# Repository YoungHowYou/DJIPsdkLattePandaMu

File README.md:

# LattePandaMu_carrier_custom
LattePandaMu大疆无人机x-port专用开发板

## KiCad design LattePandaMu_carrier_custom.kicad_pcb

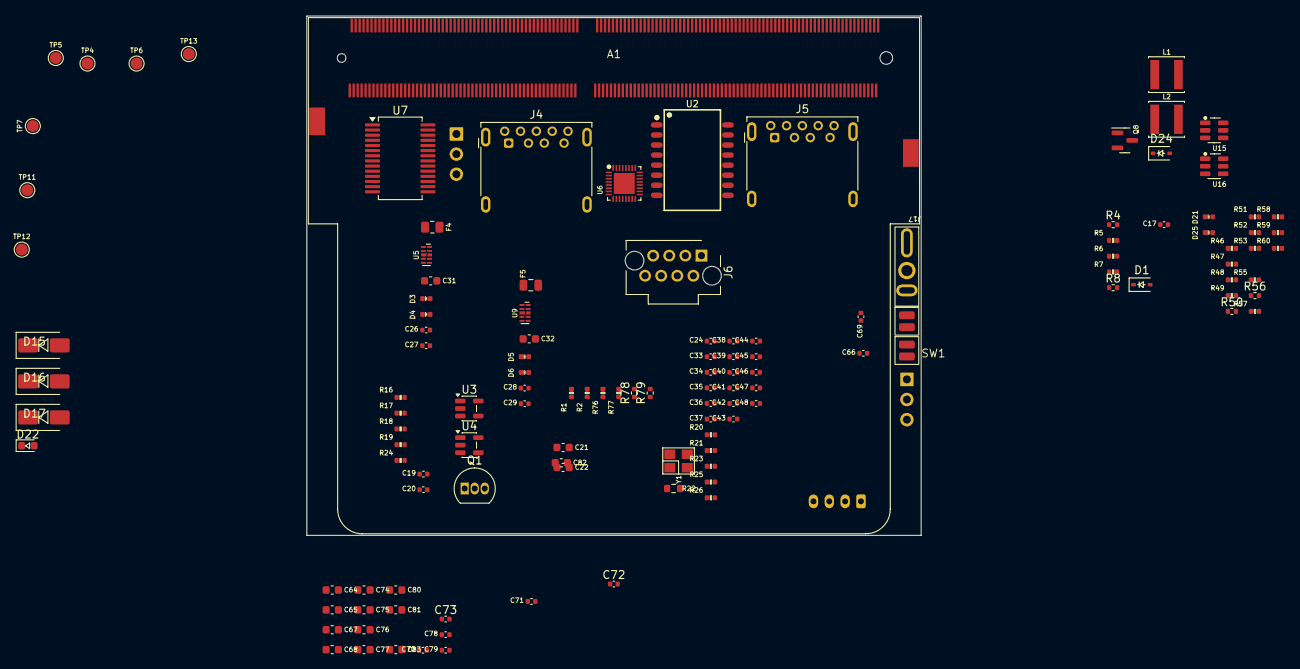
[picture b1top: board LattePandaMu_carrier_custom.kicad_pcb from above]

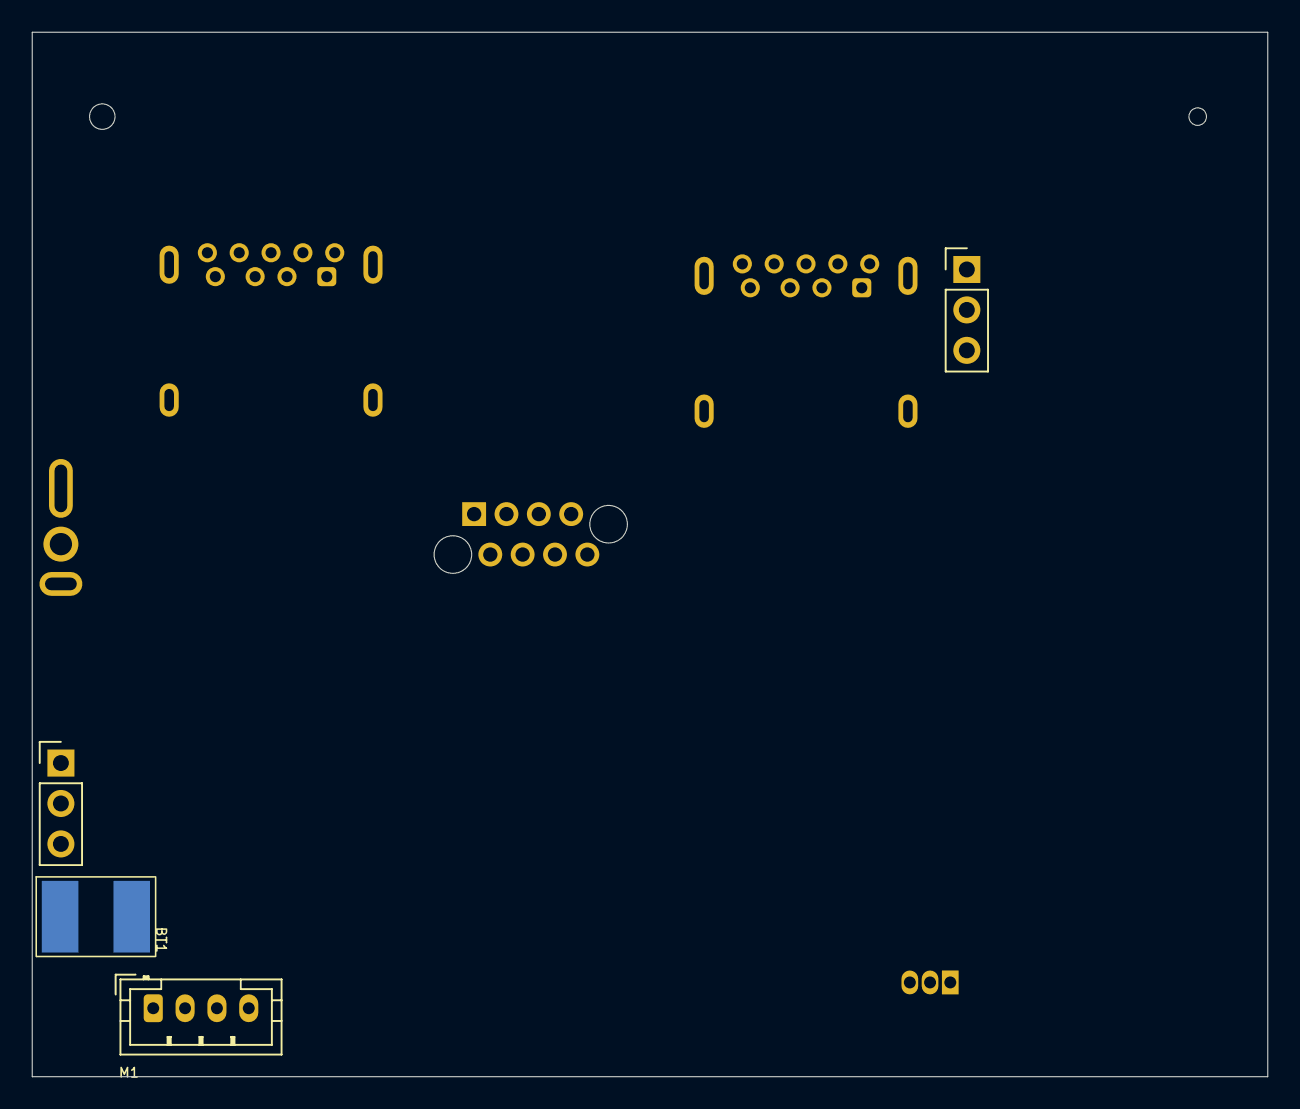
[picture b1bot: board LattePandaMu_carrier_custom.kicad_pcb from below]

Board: 4 copper layers, 77.6 x 65.6 mm, 130 parts (4 on the bottom side), 91 nets, no tracks yet.

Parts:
A1: LattePanda_Mu; LattePanda_Module_H8.0mm_Horizontal
BT1: Battery_Cell; Battery_Holder_CR1220_S8411-45R
C17, C26, C27, C28, C29, C33, C34, C35, C36, C37, C38, C39, C40, C41, C42, C43, C45, C48, C70, C71, C78, C79: 100nF/50V; C_0402_1005Metric
C19, C20, C66, C69: 1uF/16V; C_0402_1005Metric
C21, C22: 100nF; C_0603_1608Metric
C24: 1000pF/2kV; C_0402_1005Metric
C31, C32, C64, C65, C67, C68, C74, C75, C76, C77, C80, C81, C82, C83: 22uF/10V; C_0603_1608Metric
C44: 10uF/10V; C_0402_1005Metric
C46, C47, C72, C73: 12pF/50V; C_0402_1005Metric
D1: 1N5819WS; D_SOD-323
D3, D4, D5, D6, D21, D25: ESD5V0B03; D_0402_1005Metric
D15, D16, D17: SS54; D_SMA
D22: LED_G; LED_0603_1608Metric
D24: 3V3 Izt=5mA; D_SOD-323
F4: 6V/2A; R_0805_2012Metric
F5: 6V/2A; Fuse_0805_2012Metric
J1: Conn_01x03_Pin; PinHeader_1x03_P2.54mm_Vertical
J3: Conn_01x03; PinHeader_1x03_P2.54mm_Vertical
J4, J5: USB3_A; USB3_A_Molex_48393-001
J6: RJ45; RJ45_Plug_Metz_AJP92A8813
J17: Barrel_Jack_Switch; DC_Jack_DC007B_30V_10A
L1, L2: 2.2uH/4.3A; L_Sunlord_SWPA4020S
M1: Fan_4pin; JST_PH_B4B-PH-K_1x04_P2.00mm_Vertical
Q1: 2N3906; TO-92_Inline
Q8: 2N7002; SOT-23
R1, R47: 1K/1%; R_0402_1005Metric
R2, R16, R17, R18, R20, R21, R24, R49, R50, R56, R58, R78, R79: 10K/1%; R_0402_1005Metric
R4, R5, R60: 4.7K/1%; R_0402_1005Metric
R6, R8, R59: 21.5K/1%; R_0402_1005Metric
R7, R46, R48, R55: 100R/1%; R_0402_1005Metric
R19: 20K/1%; R_0402_1005Metric
R22: 2.49K/1%; R_0603_1608Metric
R23: 1M/1%; R_0402_1005Metric
R25, R26: 75/1%; R_0402_1005Metric
R51, R76, R77: 100K/1%; R_0402_1005Metric
R52, R53: 2.2K/1%; R_0402_1005Metric
R57: 75K/1%; R_0402_1005Metric
SW1, SW2: SW_Push; SW_Push_6x6x6
TP4, TP5, TP6, TP7, TP11, TP12, TP13: TestPoint; TestPoint_Pad_D1.5mm
U2: H1601-A; SOP-16_12.7x7.1-E1.27
U3: SN74LVC1G125DBV; SOT-23-5
U4: SN74LVC1G126DBV; SOT-23-5
U5, U9: ULC0524P; Diodes_UDFN-10_1.0x2.5mm_P0.5mm
U6: RTL8111H-CG-RH; QFN-32-1EP_4x4mm_P0.4mm_EP2.65x2.65mm
U7: FT232RL; SSOP-28_5.3x10.2mm_P0.65mm
U15, U16: SY8253ADC; TSOT-23-6
Y1: 25MHz; Crystal_SMD_3225-4Pin_3.2x2.5mm

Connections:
+1V0: C33.2, C34.2, C35.2, C36.2, C40.2, C44.2, U6.3 (AVDD10), U6.8 (AVDD10), U6.22 (DVDD10), U6.24 (REGOUT), U6.30 (AVDD10)
+3V3: C37.2, C41.2, C45.2, C73.1, C75.2, C77.2, C79.1, C81.2, C83.2, L2.2, R4.1, R20.1, R21.1, R50.2, R52.2, R56.2, R59.2, TP6.1, U6.11 (AVDD33), U6.23 (VDDREG), U6.32 (AVDD33)
+5V: C17.1, C19.2, C20.2, C31.2, C32.2, C72.1, C74.2, C76.2, C78.1, C80.2, C82.2, D1.1 (K), F4.1, F5.1, J3.2, L1.2, M1.2 (+), Q1.1 (E), R5.1, R16.1, R17.1, R24.2, R57.2, TP5.1, U3.5 (VCC), U4.5 (VCC), U7.4 (VCCIO)
+12V: D15.2 (A), D16.2 (A), D17.2 (A), J17.1, TP4.1
+BATT: A1.115 (VBAT), R1.1
/LattePanda Module/FAN_1_PWM: A1.2 (FAN1_PWM), R4.2, R7.1, TP12.1
/LattePanda Module/FAN_1_TAC: A1.4 (FAN1_TAC), R6.2, R8.1, TP11.1
/LattePanda Module/HSIO_0_RX+: A1.16 (HSIO0_RX+), J5.6 (SSRX+), U9.5, U9.6 (NC)
/LattePanda Module/HSIO_0_RX-: A1.18 (HSIO0_RX-), J5.5 (SSRX-), U9.4, U9.7 (NC)
/LattePanda Module/HSIO_0_TX+: A1.13 (HSIO0_TX+), C29.1
/LattePanda Module/HSIO_0_TX-: A1.15 (HSIO0_TX-), C28.1
/LattePanda Module/HSIO_1_RX+: A1.22 (HSIO1_RX+), J4.6 (SSRX+)
/LattePanda Module/HSIO_1_RX-: A1.24 (HSIO1_RX-), J4.5 (SSRX-), U5.4, U5.7 (NC)
/LattePanda Module/HSIO_1_TX+: A1.19 (HSIO1_TX+), C27.1
/LattePanda Module/HSIO_1_TX-: A1.21 (HSIO1_TX-), C26.1
/LattePanda Module/HSIO_6_RX+: A1.64 (HSIO6_RX+), C43.2
/LattePanda Module/HSIO_6_RX-: A1.66 (HSIO6_RX-), C39.2
/LattePanda Module/HSIO_6_TX+: A1.61 (HSIO6_TX+), C42.2
/LattePanda Module/HSIO_6_TX-: A1.63 (HSIO6_TX-), C38.2
/LattePanda Module/REFCLK4+: A1.94 (REFCLK4+), U6.15 (REFCLK_P)
/LattePanda Module/REFCLK4-: A1.96 (REFCLK4-), U6.16 (REFCLK_N)
/LattePanda Module/SOC_UART0_RX: A1.137 (UART0_RXD), R16.2, R18.2, U4.2
/LattePanda Module/SOC_UART0_TX: A1.139 (UART0_TXD), R17.2, U3.4
/LattePanda Module/USB_2_P1+: A1.69 (USB2_P1+), D5.2 (A2), J5.3 (D+)
/LattePanda Module/USB_2_P1-: A1.67 (USB2_P1-), D6.2 (A2), J5.2 (D-)
/LattePanda Module/USB_2_P2+: A1.75 (USB2_P2+), D4.2 (A2), J4.3 (D+)
/LattePanda Module/USB_2_P2-: A1.73 (USB2_P2-), D3.2 (A2), J4.2 (D-)
/LattePanda Module/USB_2_P5+: A1.111 (USB2_P5+), U7.15 (USBD+)
/LattePanda Module/USB_2_P5-: A1.109 (USB2_P5-), U7.16 (USBD-)
/LattePanda Module/~PLT_RST: A1.105 (~PLTRST), U6.19 (PERSTB)
/LattePanda Module/~PWR_LED/~PSON: A1.5 (SLS_S0), R46.1, R47.1
/LattePanda Module/~PWR_SW: A1.1 (~PWRBTN), R48.2
/LattePanda Module/~RST_SW: A1.3 (~RSTBTN), R55.2
/usb转ttl3.3vUART/RX: J6.8, U7.5 (RXD)
/usb转ttl3.3vUART/TX: J6.7, U7.1 (TXD)
/千兆网/HSI+: C42.1, U6.13 (HSIP)
/千兆网/HSI-: C38.1, U6.14 (HSIN)
/千兆网/HSO+: C43.1, U6.17 (HSOP)
/千兆网/HSO-: C39.1, U6.18 (HSON)
/千兆网/MDIN0: J6.1, U2.11
/千兆网/MDIN1: J6.3, U2.16
/千兆网/MDIP0: J6.2, U2.9
/千兆网/MDIP1: J6.6, U2.14
/电源/PWR_EN: R46.2, R51.2, U15.4 (EN), U16.4 (EN)
GND: A1.11 (GND), A1.14 (GND), A1.17 (GND), A1.20 (GND), A1.23 (GND), A1.26 (GND), A1.29 (GND), A1.32 (GND), A1.35 (GND), A1.38 (GND), A1.41 (GND), A1.44 (GND), A1.47 (GND), A1.50 (GND), A1.53 (GND), A1.56 (GND), A1.59 (GND), A1.62 (GND), A1.65 (GND), A1.68 (GND), A1.71 (GND), A1.74 (GND), A1.77 (GND), A1.80 (GND), A1.83 (GND), A1.86 (GND), A1.89 (GND), A1.92 (GND), A1.95 (GND), A1.98 (GND), A1.101 (GND), A1.107 (GND), A1.110 (GND), A1.113 (GND), A1.116 (GND), A1.135 (GND), A1.136 (GND), A1.151 (GND), A1.158 (GND), A1.167 (GND), A1.170 (GND), A1.181 (GND), A1.182 (GND), A1.188 (GND), A1.189 (GND), A1.194 (GND), A1.195 (GND), A1.200 (GND), A1.201 (GND), A1.206 (GND), A1.207 (GND), A1.212 (GND), A1.213 (GND), A1.218 (GND), A1.219 (GND), A1.224 (GND), A1.225 (GND), A1.230 (GND), A1.231 (GND), A1.236 (GND), A1.237 (GND), A1.242 (GND), A1.243 (GND), A1.248 (GND), A1.249 (GND), A1.MP (Mountinge_Pads), BT1.2 (-), C17.2, C19.1, C20.1, C21.1, C22.2, C24.1, C31.1, C32.1, C33.1, C34.1, C35.1, C36.1, C37.1, C40.1, C41.1, C44.1, C45.1, C46.1, C47.1, C48.2, C64.1, C65.1, C66.2, C67.1, C68.1, C69.2, C74.1, C75.1, C76.1, C77.1, C78.2, C79.2, C80.1, C81.1, C82.1, C83.1, D3.1 (A1), D4.1 (A1), D5.1 (A1), D6.1 (A1), D21.1 (A1), D24.2 (A), D25.1 (A1), J1.3, J3.3, J4.4 (GND), J4.7 (DRAIN), J4.10 (SHIELD), J5.4 (GND), J5.7 (DRAIN), J5.10 (SHIELD), J6.4, J6.5, J17.2, J17.3, M1.1 (-), Q8.2 (S), R8.2, R19.2, R22.1, R49.1, R51.1, R58.1, R60.1, R76.2, R77.2, R78.2, R79.2, SW1.2, SW2.2, U3.3 (GND), U4.3 (GND), U5.3 (VSS), U5.8 (VSS), U6.33 (GND), U7.7 (GND), U7.18 (GND), U7.21 (GND), U7.25 (AGND), U7.26 (TEST), U9.3 (VSS), U9.8 (VSS), U15.2 (GND), U16.2 (GND), Y1.2, Y1.4
unnamed: A1.12 (SIO_UART_RX), J1.2
unnamed: A1.10 (SIO_UART_TX), J1.1
unnamed: A1.187 (TCP0_HPD), R76.1
unnamed: A1.185 (TCP1_HPD), R77.1
unnamed: A1.133 (~BIOS_SEL), R2.1, TP7.1
unnamed: A1.100 (~CLKREQ3), R79.1
unnamed: A1.102 (~CLKREQ4), R78.1
unnamed: BT1.1 (+), R1.2
unnamed: C24.2, R25.2, R26.2
unnamed: C48.1, U2.2, U2.7
unnamed: D1.2 (A), M1.3 (Tacho), R5.2, R6.1
unnamed: C66.1, D21.2 (A2), R48.1, R50.1, SW1.1
unnamed: D22.2 (A), R52.1
unnamed: D22.1 (K), Q8.3 (D)
unnamed: C69.1, D25.2 (A2), R55.1, R56.1, SW2.1
unnamed: J3.1, R24.1, U3.2, U4.4
unnamed: C27.2, J4.9 (SSTX+), U5.2, U5.5, U5.6 (NC), U5.9 (NC)
unnamed: C26.2, J4.8 (SSTX-), U5.1, U5.10 (NC)
unnamed: F4.2, J4.1 (VBUS)
unnamed: C29.2, J5.9 (SSTX+), U9.2, U9.9 (NC)
unnamed: C28.2, J5.8 (SSTX-), U9.1, U9.10 (NC)
unnamed: F5.2, J5.1 (VBUS)
unnamed: M1.4 (PWM), R7.2
unnamed: Q1.2 (B), R18.1
unnamed: Q1.3 (C), R19.1, U3.1, U4.1
unnamed: Q8.1 (G), R47.2, R49.2
unnamed: R25.1, U2.15
unnamed: R26.1, U2.10
unnamed: C47.2, R23.2, U6.28 (CKXTAL1), Y1.1
unnamed: C46.2, R23.1, U6.29 (CKXTAL2), Y1.3
unnamed: R20.2, U6.20 (ISOLATEB)
unnamed: R21.2, U6.21 (LANWAKEB)
unnamed: U2.6, U6.2 (MDIN0)
unnamed: U2.1, U6.5 (MDIN1)
unnamed: U2.8, U6.1 (MDIP0)
unnamed: U2.3, U6.4 (MDIP1)
unnamed: R22.2, U6.31 (RSET)
unnamed: C21.2, C22.1, U7.17 (3V3OUT), U7.20 (VCC)
unnamed: C70.2, U15.1 (BOOST)
unnamed: C72.2, R57.1, R58.2, U15.3 (FB)
unnamed: C70.1, L1.1, U15.6 (SW)
unnamed: C71.2, U16.1 (BOOST)
unnamed: C73.2, R59.1, R60.2, U16.3 (FB)
unnamed: C71.1, L2.1, U16.6 (SW)
VDC: A1.250 (VIN), A1.251 (VIN), A1.252 (VIN), A1.253 (VIN), A1.254 (VIN), A1.255 (VIN), A1.256 (VIN), A1.257 (VIN), A1.258 (VIN), A1.259 (VIN), A1.260 (VIN), C64.2, C65.2, C67.2, C68.2, D15.1 (K), D16.1 (K), D17.1 (K), R53.1, U15.5 (VIN), U16.5 (VIN)
VPullup: D24.1 (K), R2.2, R53.2, TP13.1

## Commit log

2026-02-07 原理图基本完成
